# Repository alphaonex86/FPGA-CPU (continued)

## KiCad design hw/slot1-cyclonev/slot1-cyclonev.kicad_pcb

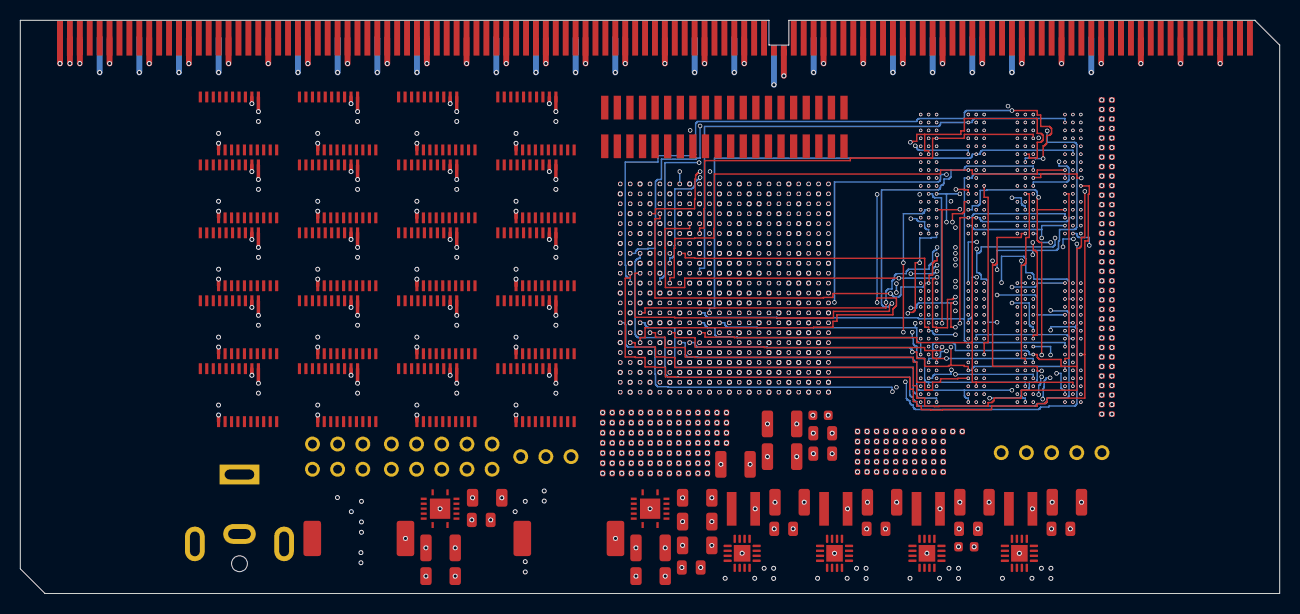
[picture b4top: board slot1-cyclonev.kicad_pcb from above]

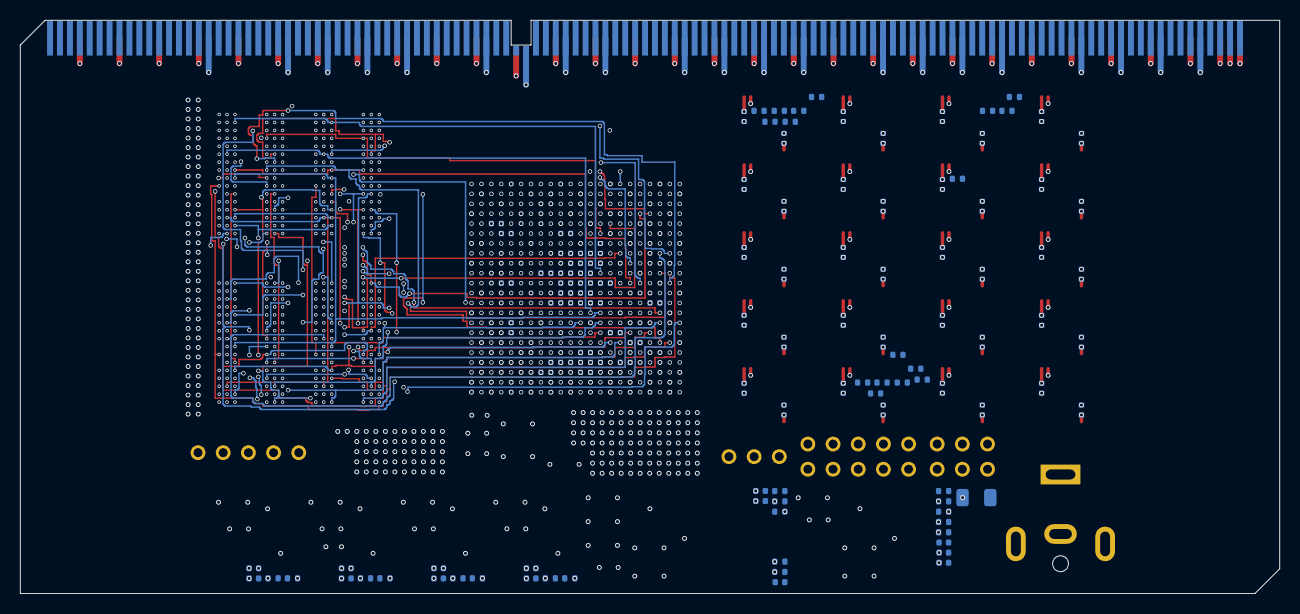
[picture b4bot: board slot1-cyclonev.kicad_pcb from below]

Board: 8 copper layers, 127.0 x 57.8 mm, 296 parts (121 on the bottom side), 432 nets.

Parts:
C1: C1; C_1210_3225Metric
C2: C2; C_0805_2012Metric
C3: C3; C_1206_3216Metric
C4: C4; C_1206_3216Metric
C5: C5; C_0402_1005Metric
C6: C6; C_0402_1005Metric
C7: C7; C_0402_1005Metric
C8: C8; C_1210_3225Metric
C9: C9; C_0805_2012Metric
C10: C10; C_1206_3216Metric
C11: C11; C_1206_3216Metric
C12: C12; C_1206_3216Metric
C13: C13; C_1206_3216Metric
C14: C14; C_0402_1005Metric
C15: C15; C_0402_1005Metric
C16: C16; C_0402_1005Metric
C17: C17; C_1210_3225Metric
C18: C18; C_0805_2012Metric
C19: C19; C_0402_1005Metric
C20: C20; C_0402_1005Metric
C21: C21; C_1210_3225Metric
C22: C22; C_0805_2012Metric
C23: C23; C_0402_1005Metric
C24: C24; C_0402_1005Metric
C25: C25; C_1210_3225Metric
C26: C26; C_0805_2012Metric
C27: C27; C_0402_1005Metric
C28: C28; C_0402_1005Metric
C29: C29; C_1210_3225Metric
C30: C30; C_0805_2012Metric
C31: C31; C_0402_1005Metric
C32: C32; C_0402_1005Metric
C33: C33; C_0402_P1.00
C34: C34; C_0402_P1.00
C35: C35; C_0402_P1.00
C36: C36; C_0402_P1.00
C37: C37; C_0402_P1.00
C38: C38; C_0402_P1.00
C39: C39; C_0402_P1.00
C40: C40; C_0402_P1.00
C41: C41; C_0402_P1.00
C42: C42; C_0402_P1.00
C43: C43; C_0402_P1.00
C44: C44; C_0402_P1.00
C45: C45; C_0402_P1.00
C46: C46; C_0402_P1.00
C47: C47; C_0402_P1.00
C48: C48; C_0402_P1.00
C49: C49; C_0402_P1.00
C50: C50; C_0402_P1.00
C51: C51; C_0402_P1.00
C52: C52; C_0402_P1.00
C53: C53; C_0402_P1.00
C54: C54; C_0402_P1.00
C55: C55; C_0402_1005Metric
C56: C56; C_0402_1005Metric
C57: C57; C_0402_1005Metric
C58: C58; C_0402_1005Metric
C59: C59; C_0402_1005Metric
C60: C60; C_0402_1005Metric
C61: C61; C_0402_1005Metric
C62: C62; C_0402_1005Metric
C63: C63; C_0402_1005Metric
C64: C64; C_0402_1005Metric
C65: C65; C_0402_1005Metric
C66: C66; C_0402_1005Metric
C67: C67; C_0402_1005Metric
C68: C68; C_0402_1005Metric
C69: C69; C_0402_1005Metric
C70: C70; C_0402_1005Metric
C71: C71; C_0402_1005Metric
C72: C72; C_0402_1005Metric
C73: C73; C_0402_1005Metric
C74: C74; C_0402_1005Metric
C75: C75; C_0402_1005Metric
C76: C76; C_0402_1005Metric
C77: C77; C_0402_1005Metric
C78: C78; C_0402_1005Metric
C79: C79; C_0402_1005Metric
C80: C80; C_0402_1005Metric
C81: C81; C_0402_1005Metric
C82: C82; C_0402_1005Metric
C83: C83; C_0402_1005Metric
C84: C84; C_0402_1005Metric
C85: C85; C_0402_1005Metric
C86: C86; C_0402_P1.00
C87: C87; C_0402_P1.00
C88: C88; C_0402_P1.00
C89: C89; C_0402_1005Metric
C90: C90; C_0402_1005Metric
C91: C91; C_0402_1005Metric
C92: C92; C_0402_1005Metric
C93: C93; C_0402_1005Metric
C94: C94; C_0402_1005Metric
C95: C95; C_0402_1005Metric
C96: C96; C_0402_P1.00
C97: C97; C_0402_1005Metric
C98: C98; C_0402_1005Metric
C99: C99; C_0402_1005Metric
C100: C100; C_0402_1005Metric
C101: C101; C_0402_1005Metric
C102: C102; C_0402_1005Metric
C103: C103; C_0402_1005Metric
C104: C104; C_0402_1005Metric
C105: C105; C_0402_P1.00
C106: C106; C_0402_P1.00
C107: C107; C_0402_P1.00
C108: C108; C_0402_P1.00
C109: C109; C_0402_P1.00
C110: C110; C_1210_3225Metric
C111: C111; C_1210_3225Metric
C112: C112; C_1210_3225Metric
C113: C113; C_0603_1608Metric
C114: C114; C_0805_2012Metric
C115: C115; C_0805_2012Metric
C116: C116; C_0402_P1.00
C117: C117; C_0402_P1.00
C118: C118; C_0402_P1.00
C119: C119; C_0402_P1.00
C120: C120; C_0402_P1.00
C121: C121; C_0402_P1.00
C122: C122; C_0402_P1.00
C123: C123; C_0402_P1.00
C124: C124; C_0402_P1.00
C125: C125; C_0402_P1.00
C126: C126; C_0402_P1.00
C127: C127; C_0402_P1.00
C128: C128; C_0402_P1.00
C129: C129; C_0402_P1.00
C130: C130; C_0402_P1.00
C131: C131; C_0402_P1.00
C132: C132; C_0402_P1.00
C133: C133; C_0402_P1.00
C134: C134; C_0402_P1.00
C135: C135; C_0402_P1.00
C136: C136; C_0402_P1.00
C137: C137; C_0402_P1.00
C138: C138; C_0402_P1.00
C139: C139; C_0402_P1.00
C140: C140; C_0402_P1.00
C141: C141; C_0402_P1.00
C142: C142; C_0402_P1.00
C143: C143; C_0402_P1.00
C144: C144; C_0402_P1.00
C145: C145; C_0402_P1.00
C146: C146; C_0402_P1.00
C147: C147; C_0402_P1.00
C148: C148; C_0402_P1.00
C149: C149; C_0402_P1.00
C150: C150; C_0402_P1.00
C151: C151; C_0402_P1.00
C152: C152; C_0402_P1.00
C153: C153; C_0402_P1.00
C154: C154; C_0402_P1.00
C155: C155; C_0402_P1.00
C156: C156; C_0402_1005Metric
C157: C157; C_0402_1005Metric
C158: C158; C_0402_1005Metric
C159: C159; C_0402_1005Metric
C160: C160; C_0402_1005Metric
C161: C161; C_0402_1005Metric
C162: C162; C_0402_1005Metric
C163: C163; C_0402_1005Metric
C164: C164; C_0402_1005Metric
C165: C165; C_0402_1005Metric
C166: C166; C_0402_1005Metric
C167: C167; C_0402_1005Metric
C168: C168; C_0402_1005Metric
C169: C169; C_0402_1005Metric
C170: C170; C_0402_1005Metric
C171: C171; C_0402_1005Metric
C172: C172; C_0402_1005Metric
C173: C173; C_0402_1005Metric
C174: C174; C_0402_1005Metric
C175: C175; C_0402_1005Metric
C176: C176; C_0402_1005Metric
C177: C177; C_0402_1005Metric
C178: C178; C_0402_1005Metric
C179: C179; C_0402_1005Metric
C180: C180; C_0402_1005Metric
C181: C181; C_0402_1005Metric
C182: C182; C_0402_1005Metric
C183: C183; C_0402_1005Metric
C184: C184; C_0402_1005Metric
C185: C185; C_0402_1005Metric
C186: C186; C_0402_1005Metric
C187: C187; C_0402_1005Metric
C188: C188; C_0402_1005Metric
C189: C189; C_0402_1005Metric
C190: C190; C_0402_1005Metric
C191: C191; C_0402_1005Metric
C192: C192; C_0402_1005Metric
C193: C193; C_0402_1005Metric
C194: C194; C_0402_1005Metric
C195: C195; C_0402_1005Metric
C196: C196; C_0402_1005Metric
C197: C197; C_0402_1005Metric
C198: C198; C_0402_1005Metric
C199: C199; C_0402_1005Metric
C200: C200; C_0402_1005Metric
C201: C201; C_0402_1005Metric
C202: C202; C_0402_1005Metric
C203: C203; C_0402_1005Metric
C204: C204; C_0402_1005Metric
C205: C205; C_0402_1005Metric
C206: C206; C_0402_1005Metric
C207: C207; C_0402_1005Metric
C208: C208; C_0402_1005Metric
C209: C209; C_0402_1005Metric
C210: C210; C_0402_1005Metric
C211: C211; C_0402_1005Metric
C212: C212; C_0402_1005Metric
C213: C213; C_0402_1005Metric
C214: C214; C_0402_1005Metric
C215: C215; C_0402_1005Metric
F1: F1; Fuse_1206_3216Metric
FB1: FB1; L_0603_1608Metric
J1: J1; Header_2x03
J2: J2; Header_2x05
J3: J3; BarrelJack_CUI_PJ-063AH_Horizontal
J4: J4; Header_1x03
J5: J5; PinHeader_2x20_P1.27mm_Vertical_SMD
L1: L1; L_Coilcraft_MSS1048-XXX
L2: L2; L_Coilcraft_MSS1048-XXX
L3: L3; L_Coilcraft_XxL4020
L4: L4; L_Coilcraft_XxL4020
L5: L5; L_Coilcraft_XxL4020
L6: L6; L_Coilcraft_XxL4020
PS1: PS1; TI_RHL0014A
PS2: PS2; TI_RHL0014A
PS3: PS3; VQFN-16-1EP_3x3mm_P0.5mm_EP1.68x1.68mm
PS4: PS4; VQFN-16-1EP_3x3mm_P0.5mm_EP1.68x1.68mm
PS5: PS5; VQFN-16-1EP_3x3mm_P0.5mm_EP1.68x1.68mm
PS6: PS6; VQFN-16-1EP_3x3mm_P0.5mm_EP1.68x1.68mm
R1: R1; R_0402_1005Metric
R2: R2; R_0402_1005Metric
R3: R3; R_0402_1005Metric
R4: R4; R_0402_1005Metric
R5: R5; R_0402_1005Metric
R6: R6; R_0402_1005Metric
R7: R7; R_0402_1005Metric
R8: R8; R_0402_1005Metric
R9: R9; R_0402_1005Metric
R10: R10; R_0402_1005Metric
R11: R11; R_0402_1005Metric
R12: R12; R_0402_1005Metric
R13: R13; R_0402_1005Metric
R14: R14; R_0402_1005Metric
R15: R15; R_0402_1005Metric
R16: R16; R_0402_1005Metric
R17: R17; R_0402_1005Metric
R18: R18; R_0402_1005Metric
RL01: RL01; R_0402_1005Metric
RL02: RL02; R_0402_1005Metric
RL03: RL03; R_0402_1005Metric
RL04: RL04; R_0402_1005Metric
RL05: RL05; R_0402_1005Metric
RL06: RL06; R_0402_1005Metric
RL07: RL07; R_0402_1005Metric
RL08: RL08; R_0402_1005Metric
RL09: RL09; R_0402_1005Metric
RL10: RL10; R_0402_1005Metric
RL11: RL11; R_0402_1005Metric
RL12: RL12; R_0402_1005Metric
RL13: RL13; R_0402_1005Metric
RL14: RL14; R_0402_1005Metric
RL15: RL15; R_0402_1005Metric
RL16: RL16; R_0402_1005Metric
RL17: RL17; R_0402_1005Metric
TR01: TR01; Translator_TSSOP20
TR02: TR02; Translator_TSSOP20
TR03: TR03; Translator_TSSOP20
TR04: TR04; Translator_TSSOP20
TR05: TR05; Translator_TSSOP20
TR06: TR06; Translator_TSSOP20
TR07: TR07; Translator_TSSOP20
TR08: TR08; Translator_TSSOP20
TR09: TR09; Translator_TSSOP20
TR10: TR10; Translator_TSSOP20
TR11: TR11; Translator_TSSOP20
TR12: TR12; Translator_TSSOP20
TR13: TR13; Translator_TSSOP20
TR14: TR14; Translator_TSSOP20
TR15: TR15; Translator_TSSOP20
TR16: TR16; Translator_TSSOP20
TR17: TR17; Translator_TSSOP20
TR18: TR18; Translator_TSSOP20
TR19: TR19; Translator_TSSOP20
TR20: TR20; Translator_TSSOP20
U1: U1; FPGA_CycloneV_5CEFA9_F484_BGA
U2: U2; SC242_CardEdge_242
U3: U3; FBGA96_x16
U4: U4; FBGA96_x16
U5: U5; FBGA96_x16
U6: U6; FBGA96_x16
U7: U7; VTT_tracker

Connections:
/A20M#: TR01.A1, U1.AA10
/ADS#: TR16.A4, U1.Y15
/AERR#: J5.33, RL15.1, U1.Y16
/AP[0]#: J5.19, RL13.1, U1.Y11
/AP[1]#: J5.31, RL14.1, U1.Y14
/A[3]#: TR03.A1, U1.AA8
/A[4]#: TR03.A2, U1.AA9
/A[5]#: TR03.A3, U1.AB10
/A[6]#: TR03.A4, U1.AB11
/A[7]#: TR03.A5, U1.AB12
/A[8]#: TR03.A6, U1.AB13
/A[9]#: TR03.A7, U1.AB15
/A[10]#: TR03.A8, U1.AB17
/A[11]#: TR04.A1, U1.AB18
/A[12]#: TR04.A2, U1.AB20
/A[13]#: TR04.A3, U1.AB21
/A[14]#: TR04.A4, U1.AB22
/A[15]#: TR04.A5, U1.AB5
/A[16]#: TR04.A6, U1.AB6
/A[17]#: TR04.A7, U1.AB7
/A[18]#: TR04.A8, U1.AB8
/A[19]#: TR05.A1, U1.K17
/A[20]#: TR05.A2, U1.K21
/A[21]#: TR05.A3, U1.K22
/A[22]#: TR05.A4, U1.L17
/A[23]#: TR05.A5, U1.L18
/A[24]#: TR05.A6, U1.L19
/A[25]#: TR05.A7, U1.L22
/A[26]#: TR05.A8, U1.M16
/A[27]#: TR06.A1, U1.M18
/A[28]#: TR06.A2, U1.M20
/A[29]#: TR06.A3, U1.M21
/A[30]#: TR06.A4, U1.M22
/A[31]#: TR06.A5, U1.M6
/A[32]#: J5.23, RL01.1, U1.M7
/A[33]#: J5.25, RL02.1, U1.N16
/A[34]#: J5.27, RL03.1, U1.N19
/A[35]#: J5.29, RL04.1, U1.N20
/BCLK: U1.M9, U2.A75
/BERR#: J5.35, RL16.1, U1.Y17
/BINIT#: J5.36, RL17.1, U1.Y19
/BNR#: TR16.A8, U1.Y20
/BPRI#: TR17.A1, U1.Y21
/BR0#: TR17.A2, U1.Y22
/BR1#: TR17.A3, U1.Y9
/CFG_CONF_DONE: J2.5, U1.K6
/CFG_DATA0: J2.9, U1.AB4
/CFG_DCLK: J2.7, U1.V3
/CFG_nCONFIG: J2.1, U1.A4
/CFG_nSTATUS: J2.3, U1.H5
/DBSY#: TR18.A1, U1.A14
/DDR3_A0: U1.L7, U3.N3, U4.N3, U5.N3, U6.N3
/DDR3_A1: U1.K7, U3.P7, U4.P7, U5.P7, U6.P7
/DDR3_A2: U1.H8, U3.P3, U4.P3, U5.P3, U6.P3
/DDR3_A3: U1.G8, U3.N2, U4.N2, U5.N2, U6.N2
/DDR3_A4: U1.J7, U3.P8, U4.P8, U5.P8, U6.P8
/DDR3_A5: U1.J8, U3.P2, U4.P2, U5.P2, U6.P2
/DDR3_A6: U1.A10, U3.R8, U4.R8, U5.R8, U6.R8
/DDR3_A7: U1.A9, U3.R2, U4.R2, U5.R2, U6.R2
/DDR3_A8: U1.A8, U3.T8, U4.T8, U5.T8, U6.T8
/DDR3_A9: U1.A7, U3.R3, U4.R3, U5.R3, U6.R3
/DDR3_A10: U1.C6, U3.L7, U4.L7, U5.L7, U6.L7
/DDR3_A11: U1.D6, U3.R7, U4.R7, U5.R7, U6.R7
/DDR3_A12: U1.D7, U3.N7, U4.N7, U5.N7, U6.N7
/DDR3_A13: U1.C8, U3.T3, U4.T3, U5.T3, U6.T3
/DDR3_A14: U1.G6, U3.T7, U4.T7, U5.T7, U6.T7
/DDR3_A15: U1.H6, U3.M7, U4.M7, U5.M7, U6.M7
/DDR3_BA0: U1.A5, U3.M2, U4.M2, U5.M2, U6.M2
/DDR3_BA1: U1.B10, U3.N8, U4.N8, U5.N8, U6.N8
/DDR3_BA2: U1.C9, U3.M3, U4.M3, U5.M3, U6.M3
/DDR3_CAS#: U1.B6, U3.K3, U4.K3, U5.K3, U6.K3
/DDR3_CK: U1.J9, U3.J7, U4.J7, U5.J7, U6.J7
/DDR3_CK#: U1.H9, U3.K7, U4.K7, U5.K7, U6.K7
/DDR3_CKE0: U1.F14, U3.K9, U4.K9
/DDR3_CKE1: U1.B13, U5.K9, U6.K9
/DDR3_CS#0: U1.E9, U3.L2, U4.L2
/DDR3_CS#1: U1.D9, U5.L2, U6.L2
/DDR3_DM0: U1.G11, U3.E7, U5.E7
/DDR3_DM1: U1.J17, U3.D3, U5.D3
/DDR3_DM2: U1.B16, U4.E7, U6.E7
/DDR3_DM3: U1.E21, U4.D3, U6.D3
/DDR3_DQ00: U1.E12, U3.E3, U5.E3
/DDR3_DQ01: U1.D12, U3.F7, U5.F7
/DDR3_DQ02: U1.C11, U3.F2, U5.F2
/DDR3_DQ03: U1.K9, U3.F8, U5.F8
/DDR3_DQ04: U1.C13, U3.H3, U5.H3
/DDR3_DQ05: U1.D13, U3.H8, U5.H8
/DDR3_DQ06: U1.B12, U3.G2, U5.G2
/DDR3_DQ07: U1.F12, U3.H7, U5.H7
/DDR3_DQ08: U3.D7, U5.D7
/DDR3_DQ09: U3.C3, U5.C3
/DDR3_DQ10: U3.C8, U5.C8
/DDR3_DQ11: U3.C2, U5.C2
/DDR3_DQ12: U3.A7, U5.A7
/DDR3_DQ13: U3.A2, U5.A2
/DDR3_DQ14: U3.B8, U5.B8
/DDR3_DQ15: U3.A3, U5.A3
/DDR3_DQ16: U1.F13, U1.F15, U4.E3, U6.E3
/DDR3_DQ17: U1.E14, U1.E15, U4.F7, U6.F7
/DDR3_DQ18: U1.A15, U1.J11, U4.F2, U6.F2
/DDR3_DQ19: U1.A13, U1.J18, U4.F8, U6.F8
/DDR3_DQ20: U1.B15, U1.E16, U4.H3, U6.H3
/DDR3_DQ21: U1.C15, U1.D17, U4.H8, U6.H8
/DDR3_DQ22: U1.G15, U1.G17, U4.G2, U6.G2
/DDR3_DQ23: U1.C16, U1.K16, U4.H7, U6.H7
/DDR3_DQ24: U1.B21, U4.D7, U6.D7
/DDR3_DQ25: U1.C21, U4.C3, U6.C3
/DDR3_DQ26: U1.G22, U4.C8, U6.C8
/DDR3_DQ27: U1.B17, U4.C2, U6.C2
/DDR3_DQ28: U1.D19, U4.A7, U6.A7
/DDR3_DQ29: U1.E19, U4.A2, U6.A2
/DDR3_DQ30: U1.C20, U4.B8, U6.B8
/DDR3_DQ31: U1.D21, U4.A3, U6.A3
/DDR3_DQS0N: U1.G12, U3.G3, U5.G3
/DDR3_DQS0P: U1.H11, U3.F3, U5.F3
/DDR3_DQS1N: U1.J13, U3.B7, U5.B7
/DDR3_DQS1P: U1.H14, U3.C7, U5.C7
/DDR3_DQS2N: U1.H18, U4.G3, U6.G3
/DDR3_DQS2P: U1.G18, U4.F3, U6.F3
/DDR3_DQS3N: U1.J22, U4.B7, U6.B7
/DDR3_DQS3P: U1.J21, U4.C7, U6.C7
/DDR3_ODT0: U1.L8, U3.K1, U4.K1
/DDR3_ODT1: U1.A12, U5.K1, U6.K1
/DDR3_RAS#: U1.B7, U3.J3, U4.J3, U5.J3, U6.J3
/DDR3_RESET#: U1.J19, U3.T2, U4.T2, U5.T2, U6.T2
/DDR3_WE#: U1.F7, U3.L3, U4.L3, U5.L3, U6.L3
/DEFER#: TR18.A2, U1.B18
/DEP[0]#: J5.3, RL05.1, U1.V9
/DEP[1]#: J5.5, RL06.1, U1.W16
/DEP[2]#: J5.7, RL07.1, U1.W19
/DEP[3]#: J5.9, RL08.1, U1.W21
/DEP[4]#: J5.11, RL09.1, U1.W22
/DEP[5]#: J5.13, RL10.1, U1.W8
/DEP[6]#: J5.15, RL11.1, U1.W9
/DEP[7]#: J5.17, RL12.1, U1.Y10
/DRDY#: TR18.A3, U1.B20
/D[0]#: TR07.A2, U1.N21
/D[1]#: TR07.A3, U1.N6
/D[2]#: TR07.A4, U1.N8
/D[3]#: TR07.A5, U1.N9
/D[4]#: TR07.A6, U1.P12
/D[5]#: TR07.A7, U1.P14
/D[6]#: TR07.A8, U1.P16
/D[7]#: TR08.A1, U1.P17
/D[8]#: TR08.A2, U1.P18
/D[9]#: TR08.A3, U1.P19
/D[10]#: TR08.A4, U1.P22
/D[11]#: TR08.A5, U1.P6
/D[12]#: TR08.A6, U1.P7
/D[13]#: TR08.A7, U1.P8
/D[14]#: TR08.A8, U1.P9
/D[15]#: TR09.A1, U1.R10
/D[16]#: TR09.A2, U1.R11
/D[17]#: TR09.A3, U1.R12
/D[18]#: TR09.A4, U1.R14
/D[19]#: TR09.A5, U1.R15
/D[20]#: TR09.A6, U1.R16
/D[21]#: TR09.A7, U1.R17
/D[22]#: TR09.A8, U1.R21
/D[23]#: TR10.A1, U1.R22
/D[24]#: TR10.A2, U1.R5
/D[25]#: TR10.A3, U1.R6
/D[26]#: TR10.A4, U1.R7
/D[27]#: TR10.A5, U1.R9
/D[28]#: TR10.A6, U1.T10
/D[29]#: TR10.A7, U1.T12
/D[30]#: TR10.A8, U1.T13
/D[31]#: TR11.A1, U1.T14
/D[32]#: TR11.A2, U1.T15
/D[33]#: TR11.A3, U1.T17
/D[34]#: TR11.A4, U1.T18
/D[35]#: TR11.A5, U1.T19
/D[36]#: TR11.A6, U1.T20
/D[37]#: TR11.A7, U1.T22
/D[38]#: TR11.A8, U1.T7
/D[39]#: TR12.A1, U1.T8
/D[40]#: TR12.A2, U1.T9
/D[41]#: TR12.A3, U1.U10
/D[42]#: TR12.A4, U1.U11
/D[43]#: TR12.A5, U1.U12
/D[44]#: TR12.A6, U1.U13
/D[45]#: TR12.A7, U1.U15
/D[46]#: TR12.A8, U1.U16
/D[47]#: TR13.A1, U1.U17
/D[48]#: TR13.A2, U1.U20
/D[49]#: TR13.A3, U1.U21
/D[50]#: TR13.A4, U1.U22
/D[51]#: TR13.A5, U1.U6
/D[52]#: TR13.A6, U1.U7
/D[53]#: TR13.A7, U1.U8
/D[54]#: TR13.A8, U1.V10
/D[55]#: TR14.A1, U1.V13
/D[56]#: TR14.A2, U1.V14
/D[57]#: TR14.A3, U1.V15
/D[58]#: TR14.A4, U1.V16
/D[59]#: TR14.A5, U1.V18
/D[60]#: TR14.A6, U1.V19
/D[61]#: TR14.A7, U1.V20
/D[62]#: TR14.A8, U1.V21
/D[63]#: TR15.A1, U1.V6
/FLUSH#: TR01.A2, U1.AA12
/F_TCK: J1.1, U1.V5
/F_TDI: J1.5, U1.W5
/F_TDO: J1.6, U1.M5
/F_TMS: J1.3, U1.P5
/GND: C1.2, C2.2, C3.2, C4.2, C6.2, C7.2, C8.2, C9.2, C10.2, C11.2, C12.2, C13.2, C15.2, C16.2, C17.2, C18.2, C19.2, C20.2, C21.2, C22.2, C23.2, C24.2, C25.2, C26.2, C27.2, C28.2, C29.2, C30.2, C31.2, C32.2, C33.2, C34.2, C35.2, C36.2, C37.2, C38.2, C39.2, C40.2, C41.2, C42.2, C43.2, C44.2, C45.2, C46.2, C47.2, C48.2, C49.2, C50.2, C51.2, C52.2, C53.2, C54.2, C55.2, C56.2, C57.2, C58.2, C59.2, C60.2, C61.2, C62.2, C63.2, C64.2, C65.2, C66.2, C67.2, C68.2, C69.2, C70.2, C71.2, C72.2, C73.2, C74.2, C75.2, C76.2, C77.2, C78.2, C79.2, C80.2, C81.2, C82.2, C83.2, C84.2, C85.2, C86.2, C87.2, C88.2, C89.2, C90.2, C91.2, C92.2, C93.2, C94.2, C95.2, C96.2, C97.2, C98.2, C99.2, C100.2, C101.2, C102.2, C103.2, C104.2, C105.2, C106.2, C107.2, C108.2, C109.2, C110.2, C111.2, C112.2, C113.2, C114.2, C115.2, C116.2, C117.2, C118.2, C119.2, C120.2, C121.2, C122.2, C123.2, C124.2, C125.2, C126.2, C127.2, C128.2, C129.2, C130.2, C131.2, C132.2, C133.2, C134.2, C135.2, C136.2, C137.2, C138.2, C139.2, C140.2, C141.2, C142.2, C143.2, C144.2, C145.2, C146.2, C147.2, C148.2, C149.2, C150.2, C151.2, C152.2, C153.2, C154.2, C155.2, C156.2, C157.2, C158.2, C159.2, C160.2, C161.2, C162.2, C163.2, C164.2, C165.2, C166.2, C167.2, C168.2, C169.2, C170.2, C171.2, C172.2, C173.2, C174.2, C175.2, C176.2, C177.2, C178.2, C179.2, C180.2, C181.2, C182.2, C183.2, C184.2, C185.2, C186.2, C187.2, C188.2, C189.2, C190.2, C191.2, C192.2, C193.2, C194.2, C195.2, C196.2, C197.2, C198.2, C199.2, C200.2, C201.2, C202.2, C203.2, C204.2, C205.2, C206.2, C207.2, C208.2, C209.2, C210.2, C211.2, C212.2, C213.2, C214.2, C215.2, J1.2, J1.4, J2.2, J2.4, J2.6, J2.8, J2.10, J3.2, J4.3, J5.1, J5.4, J5.6, J5.8, J5.10, J5.12, J5.14, J5.16, J5.18, J5.20, J5.22, J5.24, J5.26, J5.28, J5.30, J5.32, J5.34, J5.37, J5.38, PS1.2, PS1.3, PS1.15, PS2.2, PS2.3, PS2.15, PS3.6, PS3.7, PS3.8, PS3.15, PS3.16, PS3.17, PS4.6, PS4.7, PS4.8, PS4.15, PS4.16, PS4.17, PS5.6, PS5.7, PS5.8, PS5.15, PS5.16, PS5.17, PS6.6, PS6.7, PS6.8, PS6.15, PS6.16, PS6.17, R2.2, R4.2, R7.2, R9.2, R12.2, R14.2, R16.2, R18.2, TR01.GND, TR02.GND, TR03.GND, TR04.GND, TR05.GND, TR06.GND, TR07.GND, TR08.GND, TR09.GND, TR10.GND, TR11.GND, TR12.GND, TR13.GND, TR14.GND, TR15.GND, TR16.GND, TR17.GND, TR18.GND, TR19.GND, TR20.GND, U1.A11, U1.A21, U1.AA3, U1.AA4, U1.AA6, U1.AA11, U1.AB1, U1.AB2, U1.AB9, U1.AB14, U1.AB19, U1.B1, U1.B2, U1.B9, U1.B14, U1.C3, U1.C4, U1.C5, U1.C17, U1.D1, U1.D2, U1.D5, U1.D10, U1.D20, U1.E3, U1.E4, U1.E13, U1.F1, U1.F2, U1.F5, U1.F6, U1.F16, U1.F17, U1.G3, U1.G4, U1.G9, U1.G19, U1.H1, U1.H2, U1.H3, U1.H4, U1.H7, U1.H12, U1.H22, U1.J3, U1.J5, U1.J15, U1.J20, U1.K1, U1.K2, U1.K4, U1.K8, U1.K10, U1.K12, U1.K14, U1.L3, U1.L5, U1.L11, U1.L13, U1.L15, U1.L21, U1.M1, U1.M2, U1.M4, U1.M10, U1.M12, U1.M14, U1.N3, U1.N5, U1.N7, U1.N11, U1.N13, U1.N15, U1.N17, U1.N22, U1.P1, U1.P2, U1.P4, U1.P10, U1.R3, U1.R13, U1.T1, U1.T2, U1.T16, U1.T21, U1.U3, U1.U4, U1.U5, U1.U9, U1.V1, U1.V2, U1.V4, U1.V7, U1.V12, U1.V17, U1.V22, U1.W3, U1.W4, U1.Y1, U1.Y2, U1.Y5, U1.Y18, U2.A2, U2.A6, U2.A10, U2.A14, U2.A18, U2.A22, U2.A26, U2.A30, U2.A34, U2.A38, U2.A42, U2.A46, U2.A50, U2.A54, U2.A58, U2.A62, U2.A66, U2.A70, U2.A74, U2.A78, U2.A82, U2.A86, U2.A90, U2.A94, U2.A98, U2.A102, U2.A106, U2.A110, U2.A114, U2.A118, U3.A9, U3.B1, U3.B3, U3.B9, U3.D1, U3.D8, U3.E1, U3.E2, U3.E8, U3.F9, U3.G1, U3.G8, U3.G9, U3.J2, U3.J8, U3.M1, U3.M9, U3.P1, U3.P9, U3.T1, U3.T9, U4.A9, U4.B1, U4.B3, U4.B9, U4.D1, U4.D8, U4.E1, U4.E2, U4.E8, U4.F9, U4.G1, U4.G8, U4.G9, U4.J2, U4.J8, U4.M1, U4.M9, U4.P1, U4.P9, U4.T1, U4.T9, U5.A9, U5.B1, U5.B3, U5.B9, U5.D1, U5.D8, U5.E1, U5.E2, U5.E8, U5.F9, U5.G1, U5.G8, U5.G9, U5.J2, U5.J8, U5.M1, U5.M9, U5.P1, U5.P9, U5.T1, U5.T9, U6.A9, U6.B1, U6.B3, U6.B9, U6.D1, U6.D8, U6.E1, U6.E2, U6.E8, U6.F9, U6.G1, U6.G8, U6.G9, U6.J2, U6.J8, U6.M1, U6.M9, U6.P1, U6.P9, U6.T1, U6.T9, U7.GND
/HIT#: TR18.A4, U1.B5
/HITM#: TR18.A5, U1.E10
/IGNNE#: TR01.A3, U1.AA13
/INIT#: TR01.A4, U1.AA14
/LINK_DCLK: J5.21, U1.M8
/LINT[0]/INTR: TR01.A5, U1.AA15
/LINT[1]/NMI: TR01.A6, U1.AA17
/LOCK#: TR18.A6, U1.E7
/PG_1V1: PS2.14, PS3.13, PS4.13, PS5.13, PS6.13, R10.1
/PG_5V: PS1.14, PS2.10, R5.1
/PS1_BOOT: C5.1, PS1.13
/PS1_COMP: PS1.8, R1.1
/PS1_CZ: C7.1, R1.2
/PS1_FB: PS1.7, R3.2, R4.1
/PS1_RT: PS1.1, R2.1
/PS1_SS: C6.1, PS1.9
/PS1_SW: C5.2, L1.1, PS1.11, PS1.12
/PS2_BOOT: C14.1, PS2.13
/PS2_COMP: PS2.8, R6.1
/PS2_CZ: C16.1, R6.2
/PS2_FB: PS2.7, R8.2, R9.1
/PS2_RT: PS2.1, R7.1
/PS2_SS: C15.1, PS2.9
/PS2_SW: C14.2, L2.1, PS2.11, PS2.12
/PS3_FB: PS3.5, R11.2, R12.1
/PS3_SS: C20.1, PS3.9
/PS3_SW: L3.1, PS3.1, PS3.2, PS3.3
/PS4_FB: PS4.5, R13.2, R14.1
/PS4_SS: C24.1, PS4.9
/PS4_SW: L4.1, PS4.1, PS4.2, PS4.3
/PS5_FB: PS5.5, R15.2, R16.1
/PS5_SS: C28.1, PS5.9
/PS5_SW: L5.1, PS5.1, PS5.2, PS5.3
/PS6_FB: PS6.5, R17.2, R18.1
/PS6_SS: C32.1, PS6.9
/PS6_SW: L6.1, PS6.1, PS6.2, PS6.3
/PWRGOOD: TR01.A7, U1.AA18
/REQ[0]#: TR18.A7, U1.F10
/REQ[1]#: TR18.A8, U1.F22
/REQ[2]#: TR19.A1, U1.F9
/REQ[3]#: TR19.A2, U1.G10
/REQ[4]#: TR19.A3, U1.G13
/RESET#: TR20.A2, U1.H21
/RP#: TR19.A4, U1.G16
/RSP#: TR19.A5, U1.G21
/RS[0]#: TR19.A6, U1.H10
/RS[1]#: TR19.A7, U1.H13
/RS[2]#: TR19.A8, U1.H15
/SLP#: TR01.A8, U1.AA19
/SMI#: TR02.A1, U1.AA20
/STPCLK#: TR02.A2, U1.AA22
/S_A20M#: TR01.B1, U2.A5
/S_ADS#: TR16.B4, U2.A115
/S_AERR#: TR16.B5, U2.B118
/S_AP[0]#: TR16.B2, U2.A117
/S_AP[1]#: TR16.B3, U2.B116
/S_A[3]#: TR03.B1, U2.B98
/S_A[4]#: TR03.B2, U2.A100
/S_A[5]#: TR03.B3, U2.A97
/S_A[6]#: TR03.B4, U2.B99
/S_A[7]#: TR03.B5, U2.B96
/S_A[8]#: TR03.B6, U2.B95
/S_A[9]#: TR03.B7, U2.A99
/S_A[10]#: TR03.B8, U2.A96
/S_A[11]#: TR04.B1, U2.B92
/S_A[12]#: TR04.B2, U2.B94
/S_A[13]#: TR04.B3, U2.A93
/S_A[14]#: TR04.B4, U2.A95
/S_A[15]#: TR04.B5, U2.B90
/S_A[16]#: TR04.B6, U2.A92
/S_A[17]#: TR04.B7, U2.B91
/S_A[18]#: TR04.B8, U2.A91
/S_A[19]#: TR05.B1, U2.A89
/S_A[20]#: TR05.B2, U2.B86
/S_A[21]#: TR05.B3, U2.B87
/S_A[22]#: TR05.B4, U2.A85
/S_A[23]#: TR05.B5, U2.A87
/S_A[24]#: TR05.B6, U2.B83
/S_A[25]#: TR05.B7, U2.B88
/S_A[26]#: TR05.B8, U2.B82
/S_A[27]#: TR06.B1, U2.A84
/S_A[28]#: TR06.B2, U2.B84
/S_A[29]#: TR06.B3, U2.B80
/S_A[30]#: TR06.B4, U2.A81
/S_A[31]#: TR06.B5, U2.A83
/S_A[32]#: TR06.B6, U2.B79
/S_A[33]#: TR06.B7, U2.A79
/S_A[34]#: TR06.B8, U2.A80
/S_A[35]#: TR07.B1, U2.B78
/S_BERR#: TR16.B6, U2.A77
/S_BINIT#: TR16.B7, U2.A24
/S_BNR#: TR16.B8, U2.A101
/S_BPRI#: TR17.B1, U2.A103
/S_BR0#: TR17.B2, U2.A76
/S_BR1#: TR17.B3, U2.B75
/S_DBSY#: TR18.B1, U2.A111
/S_DEFER#: TR18.B2, U2.A105
/S_DEP[0]#: TR15.B2, U2.A25
/S_DEP[1]#: TR15.B3, U2.A27
/S_DEP[2]#: TR15.B4, U2.B26
/S_DEP[3]#: TR15.B5, U2.A28
/S_DEP[4]#: TR15.B6, U2.B27
/S_DEP[5]#: TR15.B7, U2.A29
/S_DEP[6]#: TR15.B8, U2.A31
/S_DEP[7]#: TR16.B1, U2.B28
/S_DRDY#: TR18.B3, U2.B107
/S_D[0]#: TR07.B2, U2.B72
/S_D[1]#: TR07.B3, U2.A73
/S_D[2]#: TR07.B4, U2.B71
/S_D[3]#: TR07.B5, U2.A72
/S_D[4]#: TR07.B6, U2.B70
/S_D[5]#: TR07.B7, U2.A71
/S_D[6]#: TR07.B8, U2.B68
/S_D[7]#: TR08.B1, U2.B67
/S_D[8]#: TR08.B2, U2.A69
/S_D[9]#: TR08.B3, U2.A68
/S_D[10]#: TR08.B4, U2.A65
/S_D[11]#: TR08.B5, U2.A64
/S_D[12]#: TR08.B6, U2.B66
/S_D[13]#: TR08.B7, U2.A63
/S_D[14]#: TR08.B8, U2.A67
/S_D[15]#: TR09.B1, U2.B64
/S_D[16]#: TR09.B2, U2.A61
/S_D[17]#: TR09.B3, U2.B63
/S_D[18]#: TR09.B4, U2.B60
/S_D[19]#: TR09.B5, U2.B59
/S_D[20]#: TR09.B6, U2.B62
/S_D[21]#: TR09.B7, U2.A60
/S_D[22]#: TR09.B8, U2.B58
/S_D[23]#: TR10.B1, U2.A59
/S_D[24]#: TR10.B2, U2.A57
/S_D[25]#: TR10.B3, U2.B56
/S_D[26]#: TR10.B4, U2.B55
/S_D[27]#: TR10.B5, U2.A56
/S_D[28]#: TR10.B6, U2.B52
/S_D[29]#: TR10.B7, U2.B54
/S_D[30]#: TR10.B8, U2.A55
/S_D[31]#: TR11.B1, U2.A53
/S_D[32]#: TR11.B2, U2.B51
/S_D[33]#: TR11.B3, U2.A51
/S_D[34]#: TR11.B4, U2.B48
/S_D[35]#: TR11.B5, U2.A52
/S_D[36]#: TR11.B6, U2.B46
/S_D[37]#: TR11.B7, U2.A49
/S_D[38]#: TR11.B8, U2.B50
/S_D[39]#: TR12.B1, U2.A45
/S_D[40]#: TR12.B2, U2.B47
/S_D[41]#: TR12.B3, U2.B42
/S_D[42]#: TR12.B4, U2.A43
/S_D[43]#: TR12.B5, U2.A48
/S_D[44]#: TR12.B6, U2.B44
/S_D[45]#: TR12.B7, U2.A44
/S_D[46]#: TR12.B8, U2.A39
/S_D[47]#: TR13.B1, U2.B43
/S_D[48]#: TR13.B2, U2.B39
/S_D[49]#: TR13.B3, U2.A40
/S_D[50]#: TR13.B4, U2.B35
/S_D[51]#: TR13.B5, U2.A41
/S_D[52]#: TR13.B6, U2.B40
/S_D[53]#: TR13.B7, U2.A36
/S_D[54]#: TR13.B8, U2.B36
/S_D[55]#: TR14.B1, U2.A33
/S_D[56]#: TR14.B2, U2.B34
/S_D[57]#: TR14.B3, U2.A37
/S_D[58]#: TR14.B4, U2.B31
/S_D[59]#: TR14.B5, U2.B38
/S_D[60]#: TR14.B6, U2.A35
/S_D[61]#: TR14.B7, U2.A32
/S_D[62]#: TR14.B8, U2.B30
/S_D[63]#: TR15.B1, U2.B32
/S_FLUSH#: TR01.B2, U2.B2
/S_HIT#: TR18.B4, U2.B110
/S_HITM#: TR18.B5, U2.A109
/S_IGNNE#: TR01.B3, U2.A8
/S_INIT#: TR01.B4, U2.B4
/S_LINT[0]/INTR: TR01.B5, U2.A17
/S_LINT[1]/NMI: TR01.B6, U2.B16
/S_LOCK#: TR18.B6, U2.B106
/S_PWRGOOD: TR01.B7, U2.A12
/S_REQ[0]#: TR18.B7, U2.B102
/S_REQ[1]#: TR18.B8, U2.B103
/S_REQ[2]#: TR19.B1, U2.A107
/S_REQ[3]#: TR19.B2, U2.A108
/S_REQ[4]#: TR19.B3, U2.B104
/S_RESET#: TR20.B2, U2.B74
/S_RP#: TR19.B4, U2.B114
/S_RSP#: TR19.B5, U2.B115
/S_RS[0]#: TR19.B6, U2.B108
/S_RS[1]#: TR19.B7, U2.A112
/S_RS[2]#: TR19.B8, U2.B111
/S_SLP#: TR01.B8, U2.B8
/S_SMI#: TR02.B1, U2.B3
/S_STPCLK#: TR02.B2, U2.B6
/S_THERMTRIP#: TR02.B3, U2.A15
/S_TRDY#: TR20.B1, U2.A104
/TA_AERR#: RL15.2, TR16.A5
/TA_AP[0]#: RL13.2, TR16.A2
/TA_AP[1]#: RL14.2, TR16.A3
/TA_A[32]#: RL01.2, TR06.A6
/TA_A[33]#: RL02.2, TR06.A7
/TA_A[34]#: RL03.2, TR06.A8
/TA_A[35]#: RL04.2, TR07.A1
/TA_BERR#: RL16.2, TR16.A6
/TA_BINIT#: RL17.2, TR16.A7
/TA_DEP[0]#: RL05.2, TR15.A2
/TA_DEP[1]#: RL06.2, TR15.A3
/TA_DEP[2]#: RL07.2, TR15.A4
/TA_DEP[3]#: RL08.2, TR15.A5
/TA_DEP[4]#: RL09.2, TR15.A6
/TA_DEP[5]#: RL10.2, TR15.A7
/TA_DEP[6]#: RL11.2, TR15.A8
/TA_DEP[7]#: RL12.2, TR16.A1
/THERMTRIP#: TR02.A3, U1.AA7
/TRDY#: TR20.A1, U1.H16
/V5: C3.1, C4.1, C8.1, C9.1, C17.1, C19.1, C21.1, C23.1, C25.1, C27.1, C29.1, C31.1, L1.2, PS2.4, PS2.5, PS2.6, PS3.10, PS3.11, PS3.12, PS4.10, PS4.11, PS4.12, PS5.10, PS5.11, PS5.12, PS6.10, PS6.11, PS6.12, R3.1, R5.2, R10.2
/V12: C1.1, C2.1, F1.2, PS1.4, PS1.5, PS1.6
/V12_IN: F1.1, J3.1
/VCCA_FPLL25: C108.1, FB1.2, U1.F4, U1.H19, U1.M3, U1.T3, U1.T5, U1.U18
/VCCCORE: J4.1, U2.B13, U2.B17, U2.B25, U2.B29, U2.B33, U2.B37, U2.B45, U2.B49, U2.B53, U2.B57, U2.B65, U2.B69, U2.B73, U2.B77, U2.B85, U2.B89, U2.B93, U2.B97, U2.B105
/VCCIO33: C22.1, C86.1, C87.1, C88.1, C89.1, C90.1, C91.1, C92.1, C93.1, C94.1, C95.1, C114.1, C116.1, C118.1, C120.1, C122.1, C124.1, C126.1, C128.1, C130.1, C132.1, C134.1, C136.1, C138.1, C140.1, C142.1, C144.1, C146.1, C148.1, L4.2, PS4.14, R13.1, TR01.VCCA, TR02.VCCA, TR03.VCCA, TR04.VCCA, TR05.VCCA, TR06.VCCA, TR07.VCCA, TR08.VCCA, TR09.VCCA, TR10.VCCA, TR11.VCCA, TR12.VCCA, TR13.VCCA, TR14.VCCA, TR15.VCCA, TR16.VCCA, TR17.VCCA, U1.AA16, U1.AA21, U1.K18, U1.M17, U1.M19, U1.N18, U1.P20, U1.P21, U1.R8, U1.R18, U1.T6, U1.T11, U1.U14, U1.U19, U1.W6, U1.W10, U1.W11, U1.W12, U1.W14, U1.W15, U1.W17, U1.W20, U1.Y8, U1.Y13
/VCCPGM18: C26.1, C109.1, L5.2, PS5.14, R15.1, U1.F8, U1.R19, U1.V8
/VCC_1V1: C10.1, C11.1, C12.1, C13.1, C33.1, C34.1, C35.1, C36.1, C37.1, C38.1, C39.1, C40.1, C41.1, C42.1, C43.1, C44.1, C45.1, C46.1, C47.1, C48.1, C49.1, C50.1, C51.1, C52.1, C53.1, C54.1, C55.1, C56.1, C57.1, C58.1, C59.1, C60.1, C61.1, C62.1, C63.1, C64.1, C65.1, C66.1, C67.1, C68.1, C69.1, C70.1, C71.1, C72.1, C73.1, C74.1, C75.1, C76.1, C77.1, C78.1, C79.1, C80.1, C81.1, C82.1, C83.1, C84.1, C85.1, C110.1, C111.1, C112.1, C113.1, L2.2, R8.1, U1.J4, U1.J10, U1.J12, U1.J14, U1.J16, U1.K3, U1.K5, U1.K11, U1.K13, U1.K15, U1.L4, U1.L10, U1.L12, U1.L14, U1.L16, U1.M11, U1.M13, U1.M15, U1.N4, U1.N10, U1.N12, U1.N14, U1.P3, U1.P11, U1.P13, U1.P15
/VCC_AUX25: C18.1, C105.1, C106.1, C107.1, C117.1, C119.1, FB1.1, L3.2, PS3.14, R11.1, TR01.VCCB, TR02.VCCB, U1.A3, U1.C10, U1.D8, U1.D11, U1.D14, U1.D16, U1.D18, U1.E6, U1.E11, U1.W7, U1.W13, U1.W18
/VDDR3: C30.1, C96.1, C97.1, C98.1, C99.1, C100.1, C101.1, C102.1, C103.1, C104.1, C115.1, C150.1, C152.1, C154.1, C156.1, C157.1, C158.1, C159.1, C160.1, C161.1, C162.1, C163.1, C164.1, C165.1, C166.1, C167.1, C168.1, C169.1, C171.1, C172.1, C173.1, C174.1, C175.1, C176.1, C177.1, C178.1, C179.1, C180.1, C181.1, C182.1, C183.1, C184.1, C186.1, C187.1, C188.1, C189.1, C190.1, C191.1, C192.1, C193.1, C194.1, C195.1, C196.1, C197.1, C198.1, C199.1, C201.1, C202.1, C203.1, C204.1, C205.1, C206.1, C207.1, C208.1, C209.1, C210.1, C211.1, C212.1, C213.1, C214.1, L6.2, PS6.14, R17.1, TR18.VCCA, TR19.VCCA, TR20.VCCA, U1.A6, U1.A16, U1.B19, U1.C7, U1.C12, U1.C22, U1.D15, U1.E8, U1.E18, U1.F11, U1.F21, U1.G7, U1.G14, U1.H17, U3.A1, U3.A8, U3.B2, U3.C1, U3.C9, U3.D2, U3.D9, U3.E9, U3.F1, U3.G7, U3.H2, U3.H9, U3.K2, U3.K8, U3.N1, U3.N9, U3.R1, U3.R9, U4.A1, U4.A8, U4.B2, U4.C1, U4.C9, U4.D2, U4.D9, U4.E9, U4.F1, U4.G7, U4.H2, U4.H9, U4.K2, U4.K8, U4.N1, U4.N9, U4.R1, U4.R9, U5.A1, U5.A8, U5.B2, U5.C1, U5.C9, U5.D2, U5.D9, U5.E9, U5.F1, U5.G7, U5.H2, U5.H9, U5.K2, U5.K8, U5.N1, U5.N9, U5.R1, U5.R9, U6.A1, U6.A8, U6.B2, U6.C1, U6.C9, U6.D2, U6.D9, U6.E9, U6.F1, U6.G7, U6.H2, U6.H9, U6.K2, U6.K8, U6.N1, U6.N9, U6.R1, U6.R9, U7.VDDQ_REF, U7.VIN
/VTT15: C121.1, C123.1, C125.1, C127.1, C129.1, C131.1, C133.1, C135.1, C137.1, C139.1, C141.1, C143.1, C145.1, C147.1, C149.1, C151.1, C153.1, C155.1, J4.2, TR03.VCCB, TR04.VCCB, TR05.VCCB, TR06.VCCB, TR07.VCCB, TR08.VCCB, TR09.VCCB, TR10.VCCB, TR11.VCCB, TR12.VCCB, TR13.VCCB, TR14.VCCB, TR15.VCCB, TR16.VCCB, TR17.VCCB, TR18.VCCB, TR19.VCCB, TR20.VCCB, U2.A1, U2.A3, U2.B5, U2.B9
/VTTREF0675: C170.1, C185.1, C200.1, C215.1, U1.AB16, U1.B8, U1.C14, U1.L20, U1.R20, U1.Y7, U1.Y12, U3.H1, U3.M8, U4.H1, U4.M8, U5.H1, U5.M8, U6.H1, U6.M8, U7.VTT, U7.VTTSNS

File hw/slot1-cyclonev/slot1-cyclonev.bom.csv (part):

"Refs","Value","Footprint","Qty","DNP"
"C1","10uF/25V","Capacitor_SMD:C_1210_3225Metric","1",""
"C2","4.7uF/25V","Capacitor_SMD:C_0805_2012Metric","1",""
"C3","22uF/10V","Capacitor_SMD:C_1206_3216Metric","1",""
"C4","22uF/10V","Capacitor_SMD:C_1206_3216Metric","1",""
"C5","100nF","Capacitor_SMD:C_0402_1005Metric","1",""
"C6","10nF","Capacitor_SMD:C_0402_1005Metric","1",""
"C7","27nF","Capacitor_SMD:C_0402_1005Metric","1",""
"C8","10uF/25V","Capacitor_SMD:C_1210_3225Metric","1",""
"C9","4.7uF/25V","Capacitor_SMD:C_0805_2012Metric","1",""
"C10","47uF/6.3V","Capacitor_SMD:C_1206_3216Metric","1",""
"C11","47uF/6.3V","Capacitor_SMD:C_1206_3216Metric","1",""
"C12","47uF/6.3V","Capacitor_SMD:C_1206_3216Metric","1",""
"C13","47uF/6.3V","Capacitor_SMD:C_1206_3216Metric","1",""
"C14","100nF","Capacitor_SMD:C_0402_1005Metric","1",""
"C15","10nF","Capacitor_SMD:C_0402_1005Metric","1",""
"C16","22nF","Capacitor_SMD:C_0402_1005Metric","1",""
"C17","10uF/25V","Capacitor_SMD:C_1210_3225Metric","1",""
"C18","22uF/6.3V","Capacitor_SMD:C_0805_2012Metric","1",""
"C19","100nF","Capacitor_SMD:C_0402_1005Metric","1",""
"C20","3.3nF","Capacitor_SMD:C_0402_1005Metric","1",""
"C21","10uF/25V","Capacitor_SMD:C_1210_3225Metric","1",""
"C22","22uF/6.3V","Capacitor_SMD:C_0805_2012Metric","1",""
"C23","100nF","Capacitor_SMD:C_0402_1005Metric","1",""
"C24","3.3nF","Capacitor_SMD:C_0402_1005Metric","1",""
"C25","10uF/25V","Capacitor_SMD:C_1210_3225Metric","1",""
"C26","22uF/6.3V","Capacitor_SMD:C_0805_2012Metric","1",""
"C27","100nF","Capacitor_SMD:C_0402_1005Metric","1",""
"C28","3.3nF","Capacitor_SMD:C_0402_1005Metric","1",""
"C29","10uF/25V","Capacitor_SMD:C_1210_3225Metric","1",""
"C30","22uF/6.3V","Capacitor_SMD:C_0805_2012Metric","1",""
"C31","100nF","Capacitor_SMD:C_0402_1005Metric","1",""
"C32","3.3nF","Capacitor_SMD:C_0402_1005Metric","1",""
"C33","4.7nF","Pwr:C_0402_P1.00","1",""
"C34","4.7nF","Pwr:C_0402_P1.00","1",""
"C35","4.7nF","Pwr:C_0402_P1.00","1",""
"C36","4.7nF","Pwr:C_0402_P1.00","1",""
"C37","4.7nF","Pwr:C_0402_P1.00","1",""
"C38","4.7nF","Pwr:C_0402_P1.00","1",""
"C39","4.7nF","Pwr:C_0402_P1.00","1",""
"C40","4.7nF","Pwr:C_0402_P1.00","1",""
"C41","4.7nF","Pwr:C_0402_P1.00","1",""
"C42","4.7nF","Pwr:C_0402_P1.00","1",""
"C43","4.7nF","Pwr:C_0402_P1.00","1",""
"C44","4.7nF","Pwr:C_0402_P1.00","1",""
"C45","4.7nF","Pwr:C_0402_P1.00","1",""
"C46","10nF","Pwr:C_0402_P1.00","1",""
"C47","10nF","Pwr:C_0402_P1.00","1",""
"C48","10nF","Pwr:C_0402_P1.00","1",""
"C49","10nF","Pwr:C_0402_P1.00","1",""
"C50","10nF","Pwr:C_0402_P1.00","1",""
"C51","10nF","Pwr:C_0402_P1.00","1",""
"C52","10nF","Pwr:C_0402_P1.00","1",""
"C53","10nF","Pwr:C_0402_P1.00","1",""
"C54","10nF","Pwr:C_0402_P1.00","1",""
"C55","10nF","Capacitor_SMD:C_0402_1005Metric","1",""
"C56","10nF","Capacitor_SMD:C_0402_1005Metric","1",""
"C57","10nF","Capacitor_SMD:C_0402_1005Metric","1",""
"C58","10nF","Capacitor_SMD:C_0402_1005Metric","1",""
"C59","10nF","Capacitor_SMD:C_0402_1005Metric","1",""
"C60","10nF","Capacitor_SMD:C_0402_1005Metric","1",""
"C61","10nF","Capacitor_SMD:C_0402_1005Metric","1",""
"C62","10nF","Capacitor_SMD:C_0402_1005Metric","1",""
"C63","22nF","Capacitor_SMD:C_0402_1005Metric","1",""
"C64","22nF","Capacitor_SMD:C_0402_1005Metric","1",""
"C65","22nF","Capacitor_SMD:C_0402_1005Metric","1",""
"C66","22nF","Capacitor_SMD:C_0402_1005Metric","1",""
"C67","22nF","Capacitor_SMD:C_0402_1005Metric","1",""
"C68","22nF","Capacitor_SMD:C_0402_1005Metric","1",""
"C69","22nF","Capacitor_SMD:C_0402_1005Metric","1",""
"C70","22nF","Capacitor_SMD:C_0402_1005Metric","1",""
"C71","22nF","Capacitor_SMD:C_0402_1005Metric","1",""
"C72","22nF","Capacitor_SMD:C_0402_1005Metric","1",""
"C73","22nF","Capacitor_SMD:C_0402_1005Metric","1",""
"C74","22nF","Capacitor_SMD:C_0402_1005Metric","1",""
"C75","47nF","Capacitor_SMD:C_0402_1005Metric","1",""
"C76","47nF","Capacitor_SMD:C_0402_1005Metric","1",""
"C77","47nF","Capacitor_SMD:C_0402_1005Metric","1",""
"C78","47nF","Capacitor_SMD:C_0402_1005Metric","1",""
"C79","100nF","Capacitor_SMD:C_0402_1005Metric","1",""
"C80","100nF","Capacitor_SMD:C_0402_1005Metric","1",""
"C81","100nF","Capacitor_SMD:C_0402_1005Metric","1",""
"C82","220nF","Capacitor_SMD:C_0402_1005Metric","1",""
"C83","220nF","Capacitor_SMD:C_0402_1005Metric","1",""
"C84","470nF","Capacitor_SMD:C_0402_1005Metric","1",""
"C85","1uF","Capacitor_SMD:C_0402_1005Metric","1",""
"C86","2.2nF","Pwr:C_0402_P1.00","1",""
"C87","2.2nF","Pwr:C_0402_P1.00","1",""
"C88","4.7nF","Pwr:C_0402_P1.00","1",""
"C89","4.7nF","Capacitor_SMD:C_0402_1005Metric","1",""
"C90","10nF","Capacitor_SMD:C_0402_1005Metric","1",""
"C91","10nF","Capacitor_SMD:C_0402_1005Metric","1",""
"C92","22nF","Capacitor_SMD:C_0402_1005Metric","1",""
"C93","47nF","Capacitor_SMD:C_0402_1005Metric","1",""
"C94","100nF","Capacitor_SMD:C_0402_1005Metric","1",""
"C95","1uF","Capacitor_SMD:C_0402_1005Metric","1",""
"C96","2.2nF","Pwr:C_0402_P1.00","1",""
"C97","4.7nF","Capacitor_SMD:C_0402_1005Metric","1",""
"C98","4.7nF","Capacitor_SMD:C_0402_1005Metric","1",""
"C99","10nF","Capacitor_SMD:C_0402_1005Metric","1",""
"C100","10nF","Capacitor_SMD:C_0402_1005Metric","1",""
"C101","22nF","Capacitor_SMD:C_0402_1005Metric","1",""
"C102","47nF","Capacitor_SMD:C_0402_1005Metric","1",""
"C103","100nF","Capacitor_SMD:C_0402_1005Metric","1",""
"C104","1uF","Capacitor_SMD:C_0402_1005Metric","1",""
"C105","10nF","Pwr:C_0402_P1.00","1",""
"C106","100nF","Pwr:C_0402_P1.00","1",""
"C107","1uF","Pwr:C_0402_P1.00","1",""
"C108","100nF","Pwr:C_0402_P1.00","1",""
"C109","100nF","Pwr:C_0402_P1.00","1",""
"C110","100uF/6.3V","Capacitor_SMD:C_1210_3225Metric","1",""
"C111","100uF/6.3V","Capacitor_SMD:C_1210_3225Metric","1",""
"C112","100uF/6.3V","Capacitor_SMD:C_1210_3225Metric","1",""
"C113","4.7uF","Capacitor_SMD:C_0603_1608Metric","1",""
"C114","10uF","Capacitor_SMD:C_0805_2012Metric","1",""
"C115","22uF","Capacitor_SMD:C_0805_2012Metric","1",""
"C116","100nF","Pwr:C_0402_P1.00","1",""
"C117","100nF","Pwr:C_0402_P1.00","1",""
"C118","100nF","Pwr:C_0402_P1.00","1",""
"C119","100nF","Pwr:C_0402_P1.00","1",""
"C120","100nF","Pwr:C_0402_P1.00","1",""
"C121","100nF","Pwr:C_0402_P1.00","1",""
"C122","100nF","Pwr:C_0402_P1.00","1",""
"C123","100nF","Pwr:C_0402_P1.00","1",""
"C124","100nF","Pwr:C_0402_P1.00","1",""
"C125","100nF","Pwr:C_0402_P1.00","1",""
"C126","100nF","Pwr:C_0402_P1.00","1",""
"C127","100nF","Pwr:C_0402_P1.00","1",""
"C128","100nF","Pwr:C_0402_P1.00","1",""
"C129","100nF","Pwr:C_0402_P1.00","1",""
"C130","100nF","Pwr:C_0402_P1.00","1",""
"C131","100nF","Pwr:C_0402_P1.00","1",""
"C132","100nF","Pwr:C_0402_P1.00","1",""
"C133","100nF","Pwr:C_0402_P1.00","1",""
"C134","100nF","Pwr:C_0402_P1.00","1",""
"C135","100nF","Pwr:C_0402_P1.00","1",""
"C136","100nF","Pwr:C_0402_P1.00","1",""
"C137","100nF","Pwr:C_0402_P1.00","1",""
"C138","100nF","Pwr:C_0402_P1.00","1",""
"C139","100nF","Pwr:C_0402_P1.00","1",""
"C140","100nF","Pwr:C_0402_P1.00","1",""
"C141","100nF","Pwr:C_0402_P1.00","1",""
"C142","100nF","Pwr:C_0402_P1.00","1",""
"C143","100nF","Pwr:C_0402_P1.00","1",""
"C144","100nF","Pwr:C_0402_P1.00","1",""
"C145","100nF","Pwr:C_0402_P1.00","1",""
"C146","100nF","Pwr:C_0402_P1.00","1",""
"C147","100nF","Pwr:C_0402_P1.00","1",""
"C148","100nF","Pwr:C_0402_P1.00","1",""
"C149","100nF","Pwr:C_0402_P1.00","1",""
"C150","100nF","Pwr:C_0402_P1.00","1",""
"C151","100nF","Pwr:C_0402_P1.00","1",""
"C152","100nF","Pwr:C_0402_P1.00","1",""
"C153","100nF","Pwr:C_0402_P1.00","1",""
"C154","100nF","Pwr:C_0402_P1.00","1",""
"C155","100nF","Pwr:C_0402_P1.00","1",""
"C156","4.7nF","Capacitor_SMD:C_0402_1005Metric","1",""
"C157","3.3nF","Capacitor_SMD:C_0402_1005Metric","1",""
"C158","2.2nF","Capacitor_SMD:C_0402_1005Metric","1",""
"C159","2.2nF","Capacitor_SMD:C_0402_1005Metric","1",""
"C160","2.2nF","Capacitor_SMD:C_0402_1005Metric","1",""
"C161","2.2nF","Capacitor_SMD:C_0402_1005Metric","1",""
"C162","470nF","Capacitor_SMD:C_0402_1005Metric","1",""
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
